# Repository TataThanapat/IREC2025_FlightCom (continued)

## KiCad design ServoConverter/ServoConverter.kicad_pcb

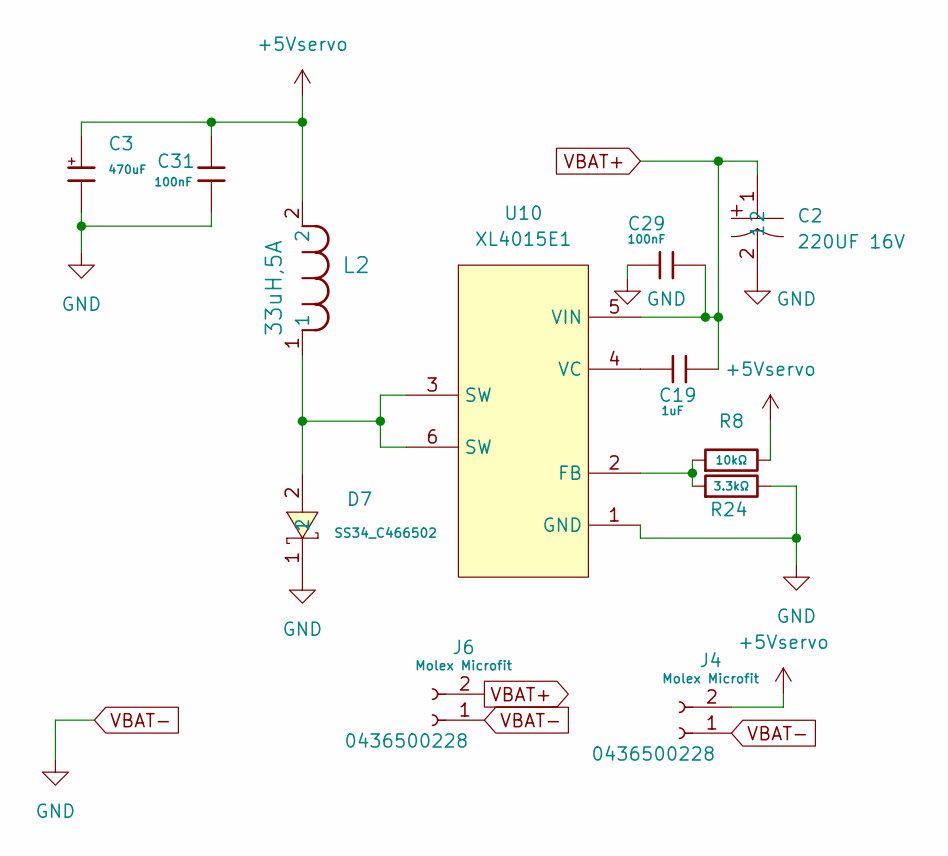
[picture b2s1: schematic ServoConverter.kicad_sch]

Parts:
C2: 220UF 16V; CAP-SMD_BD6.3-L6.6-W6.6-LS7.4-FD; LCSC Part C9900003178
C3: 470uF; CP_Elec_8x10; Voltage Rated 50V; Part EGT477M1HG16RRS0P; LCSC C3015599
C19: 1uF; C_0603; Voltage Rated 25V; Tolerance ±10%; Part CL05A105KA5NQNC; LCSC C52923
C29, C31: 100nF; C_0603; Voltage Rated 16V; Tolerance ±10%; Part CL05B104KO5NNNC; LCSC C1525
D7: SS34_C466502; DIOM7959X262N; LCSC Part C466502
J4, J6: Molex Microfit; Molex_Micro-Fit_3.0_43650-0215_1x02_P3.00mm_Vertical; Digikey Parts 0436500228
L2: 33uH,5A; L_Bourns_SRR1208_12.7x12.7mm; Digikey HCM1A1307V2-330-R
R8: 10kΩ; R_0603; Overload Voltage (Max) 75V; Tolerance ±1%; Part 0603WAF1002T5E; LCSC C25804
R24: 3.3kΩ; R_0603; Overload Voltage (Max) 75V; Tolerance ±1%; Part 0603WAF3301T5E; LCSC C22978
U10: XL4015E1; TO-263-5_L10.2-W8.9-P1.70-TL; LCSC Part C51661

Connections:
+5Vservo: C3.1, C31.2, J4.2, L2.2, R8.2
unnamed: D7.2, L2.1, U10.3 (SW), U10.6 (SW)
unnamed: R8.1, R24.1, U10.2 (FB)
unnamed: C19.1, U10.4 (VC)
VBAT+: C2.1, C19.2, C29.2, J6.2, U10.5 (VIN)
VBAT-: C2.2, C3.2, C29.1, C31.1, D7.1, J4.1, J6.1, R24.2, U10.1 (GND)

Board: 2 copper layers, 12 parts (0 on the bottom side), 6 nets, no tracks yet.

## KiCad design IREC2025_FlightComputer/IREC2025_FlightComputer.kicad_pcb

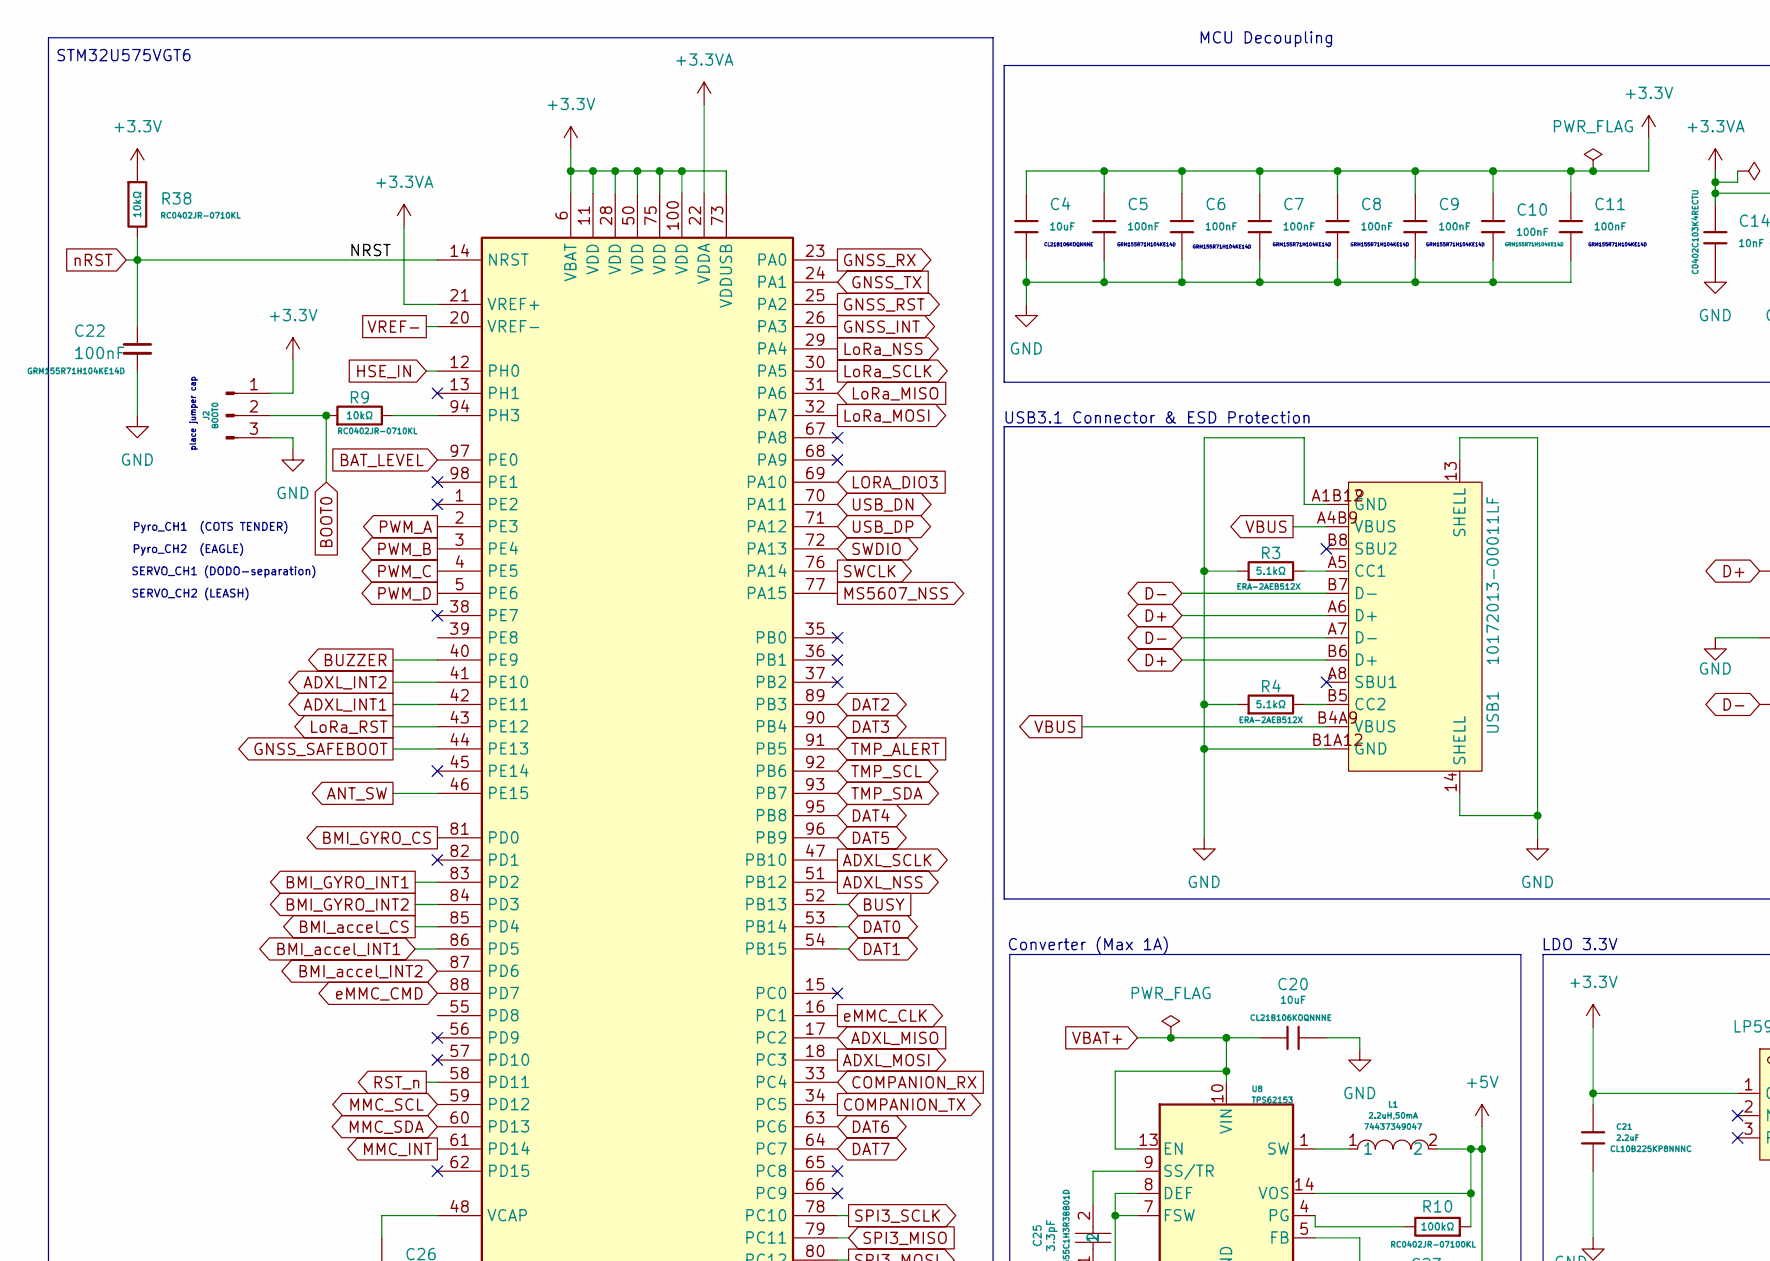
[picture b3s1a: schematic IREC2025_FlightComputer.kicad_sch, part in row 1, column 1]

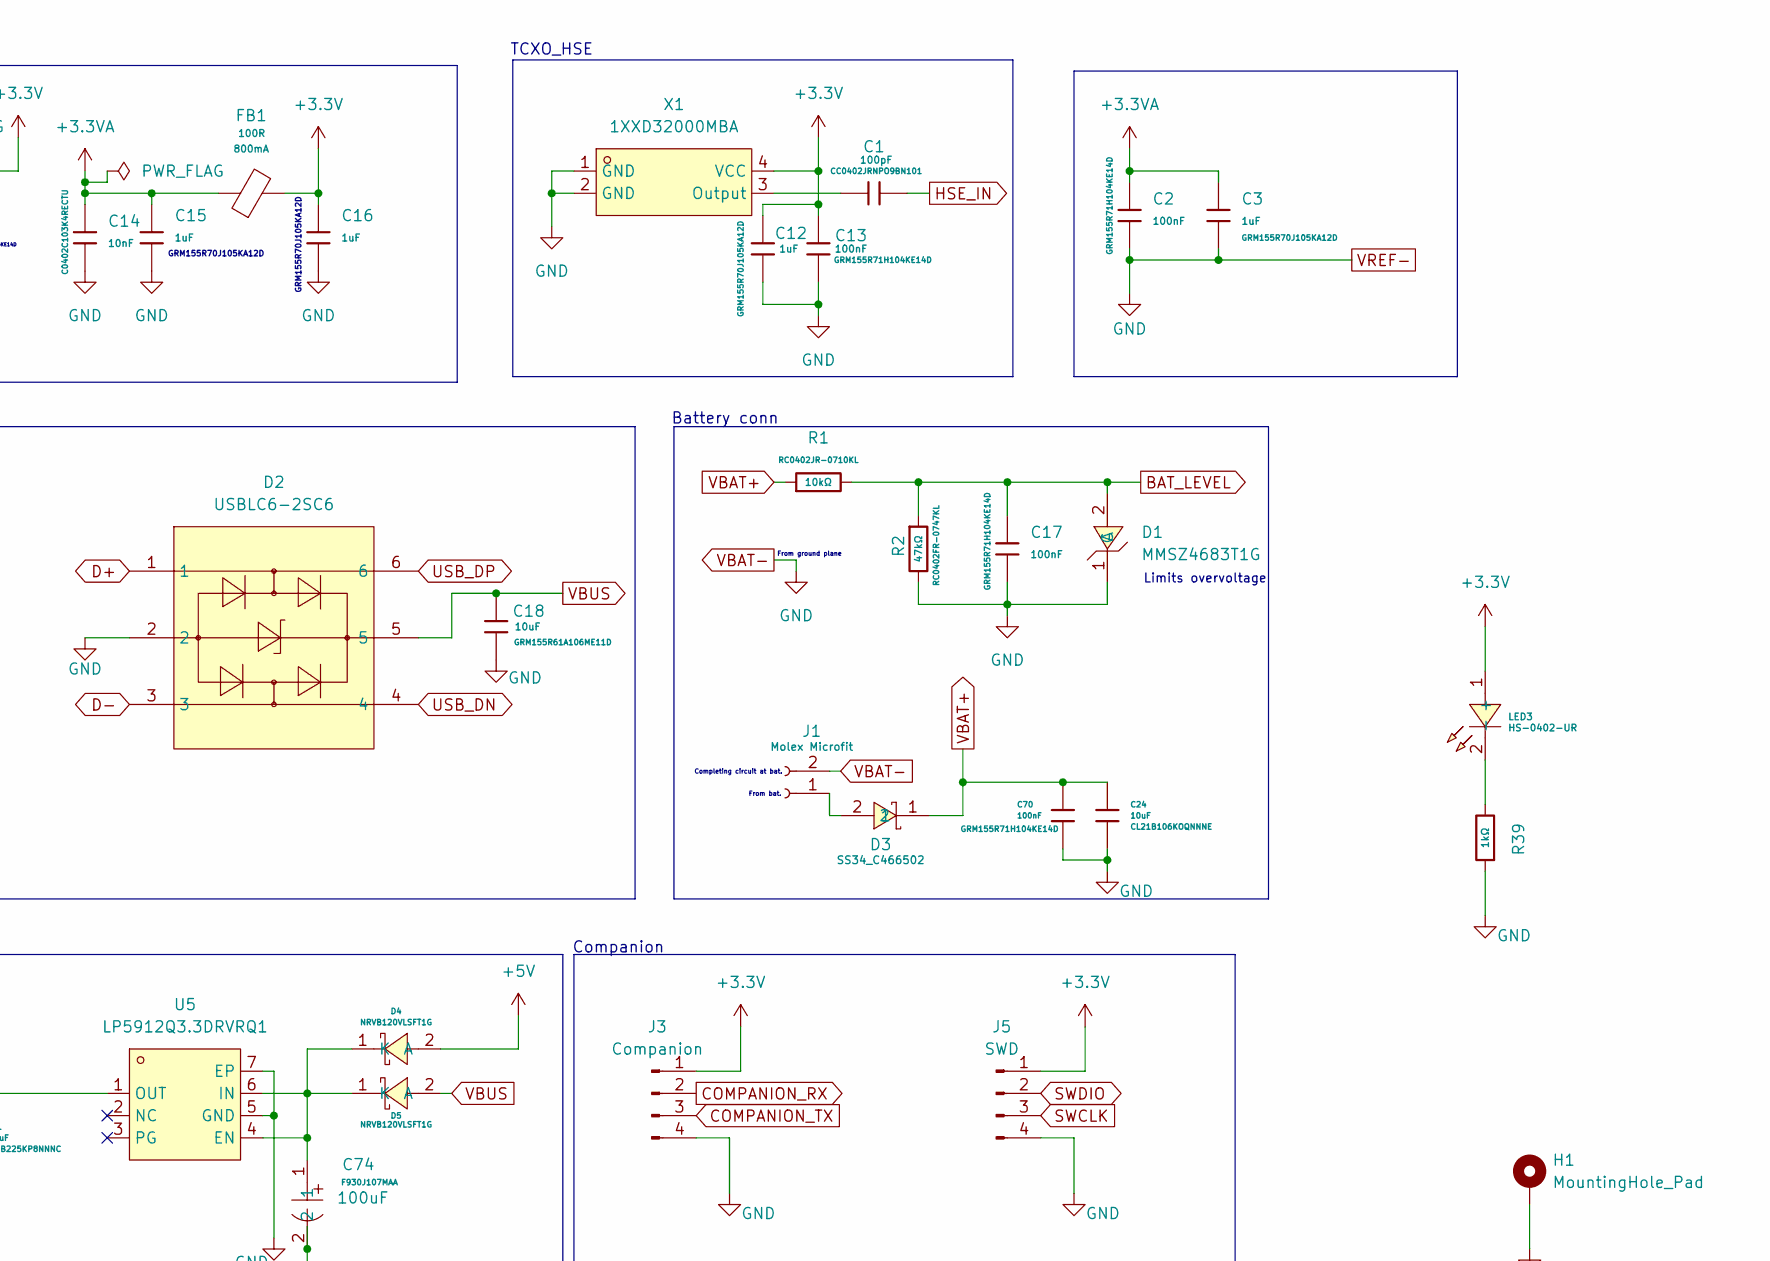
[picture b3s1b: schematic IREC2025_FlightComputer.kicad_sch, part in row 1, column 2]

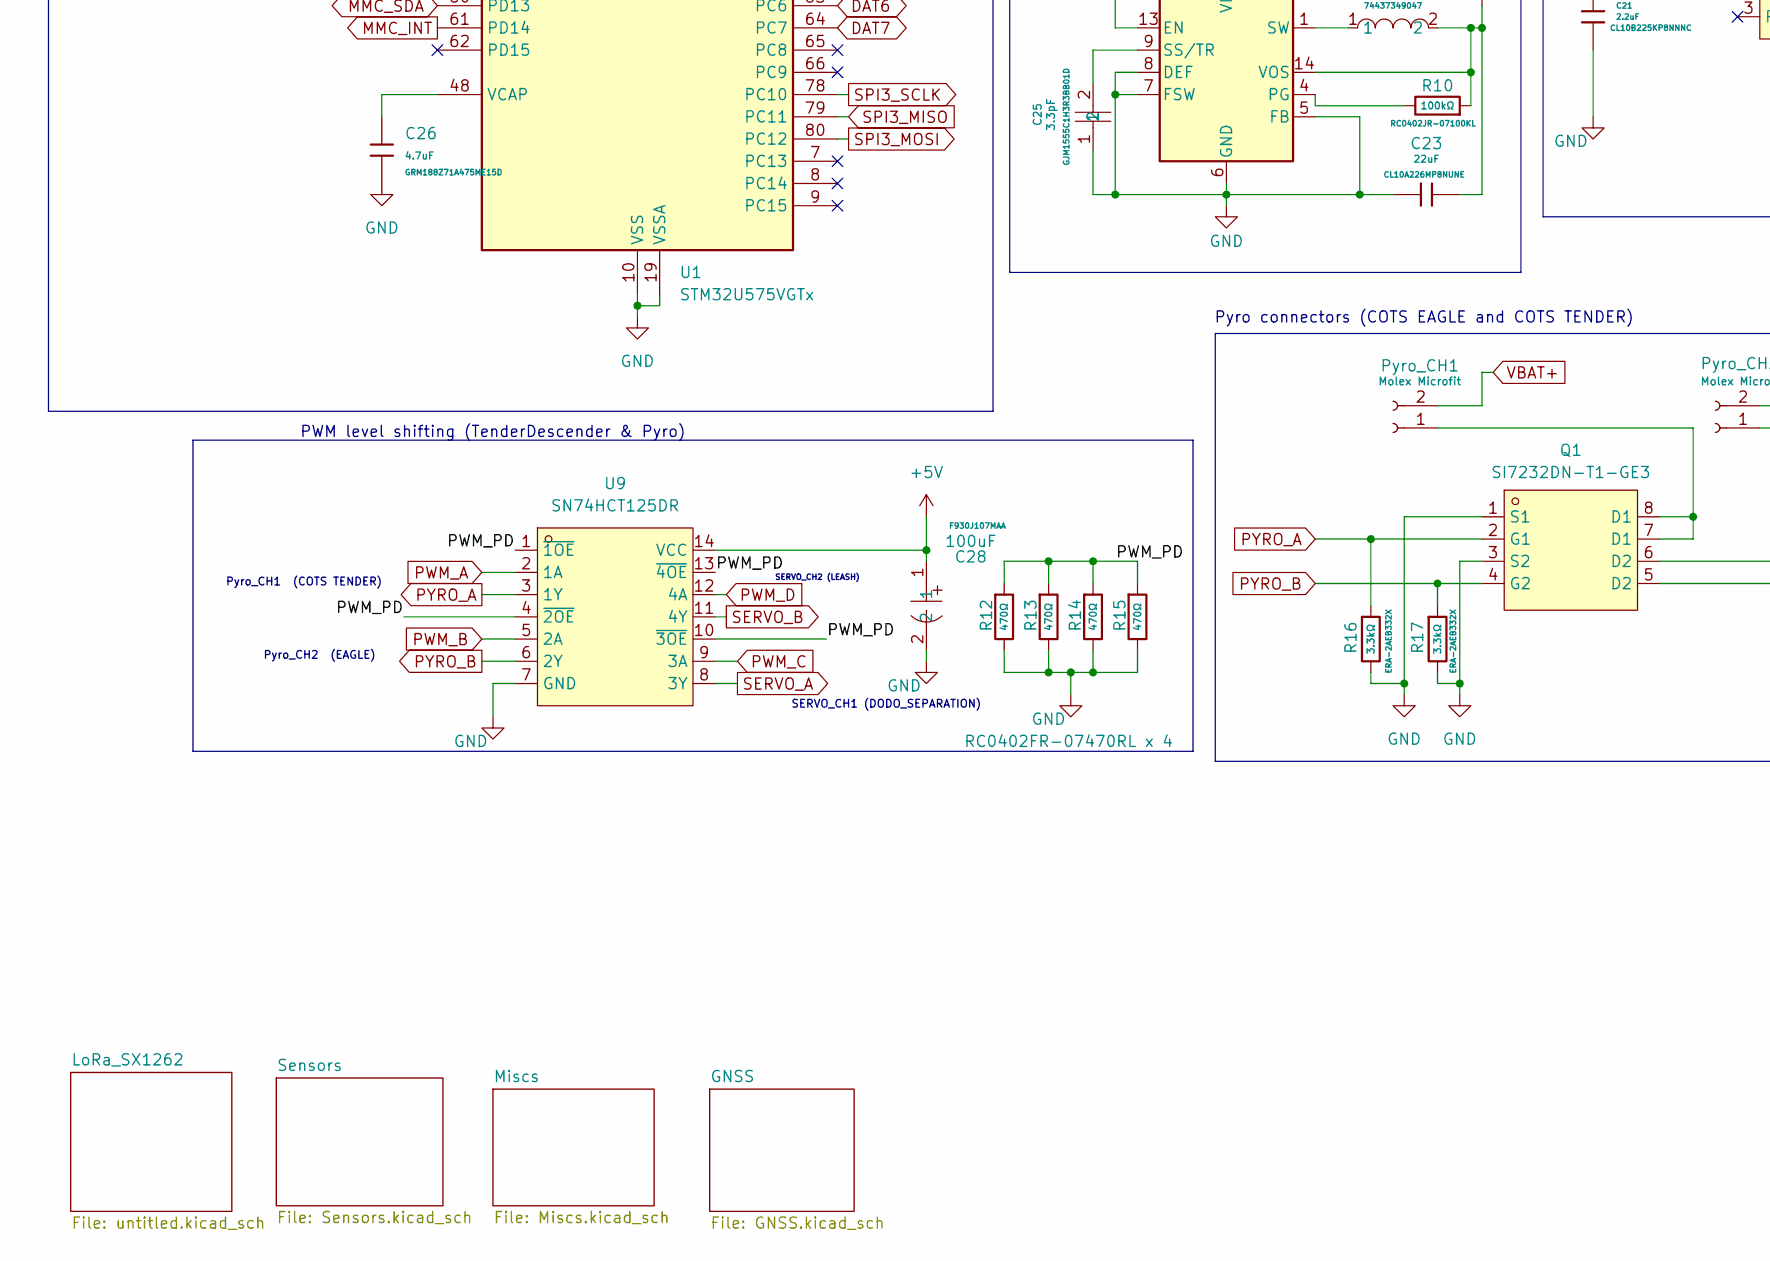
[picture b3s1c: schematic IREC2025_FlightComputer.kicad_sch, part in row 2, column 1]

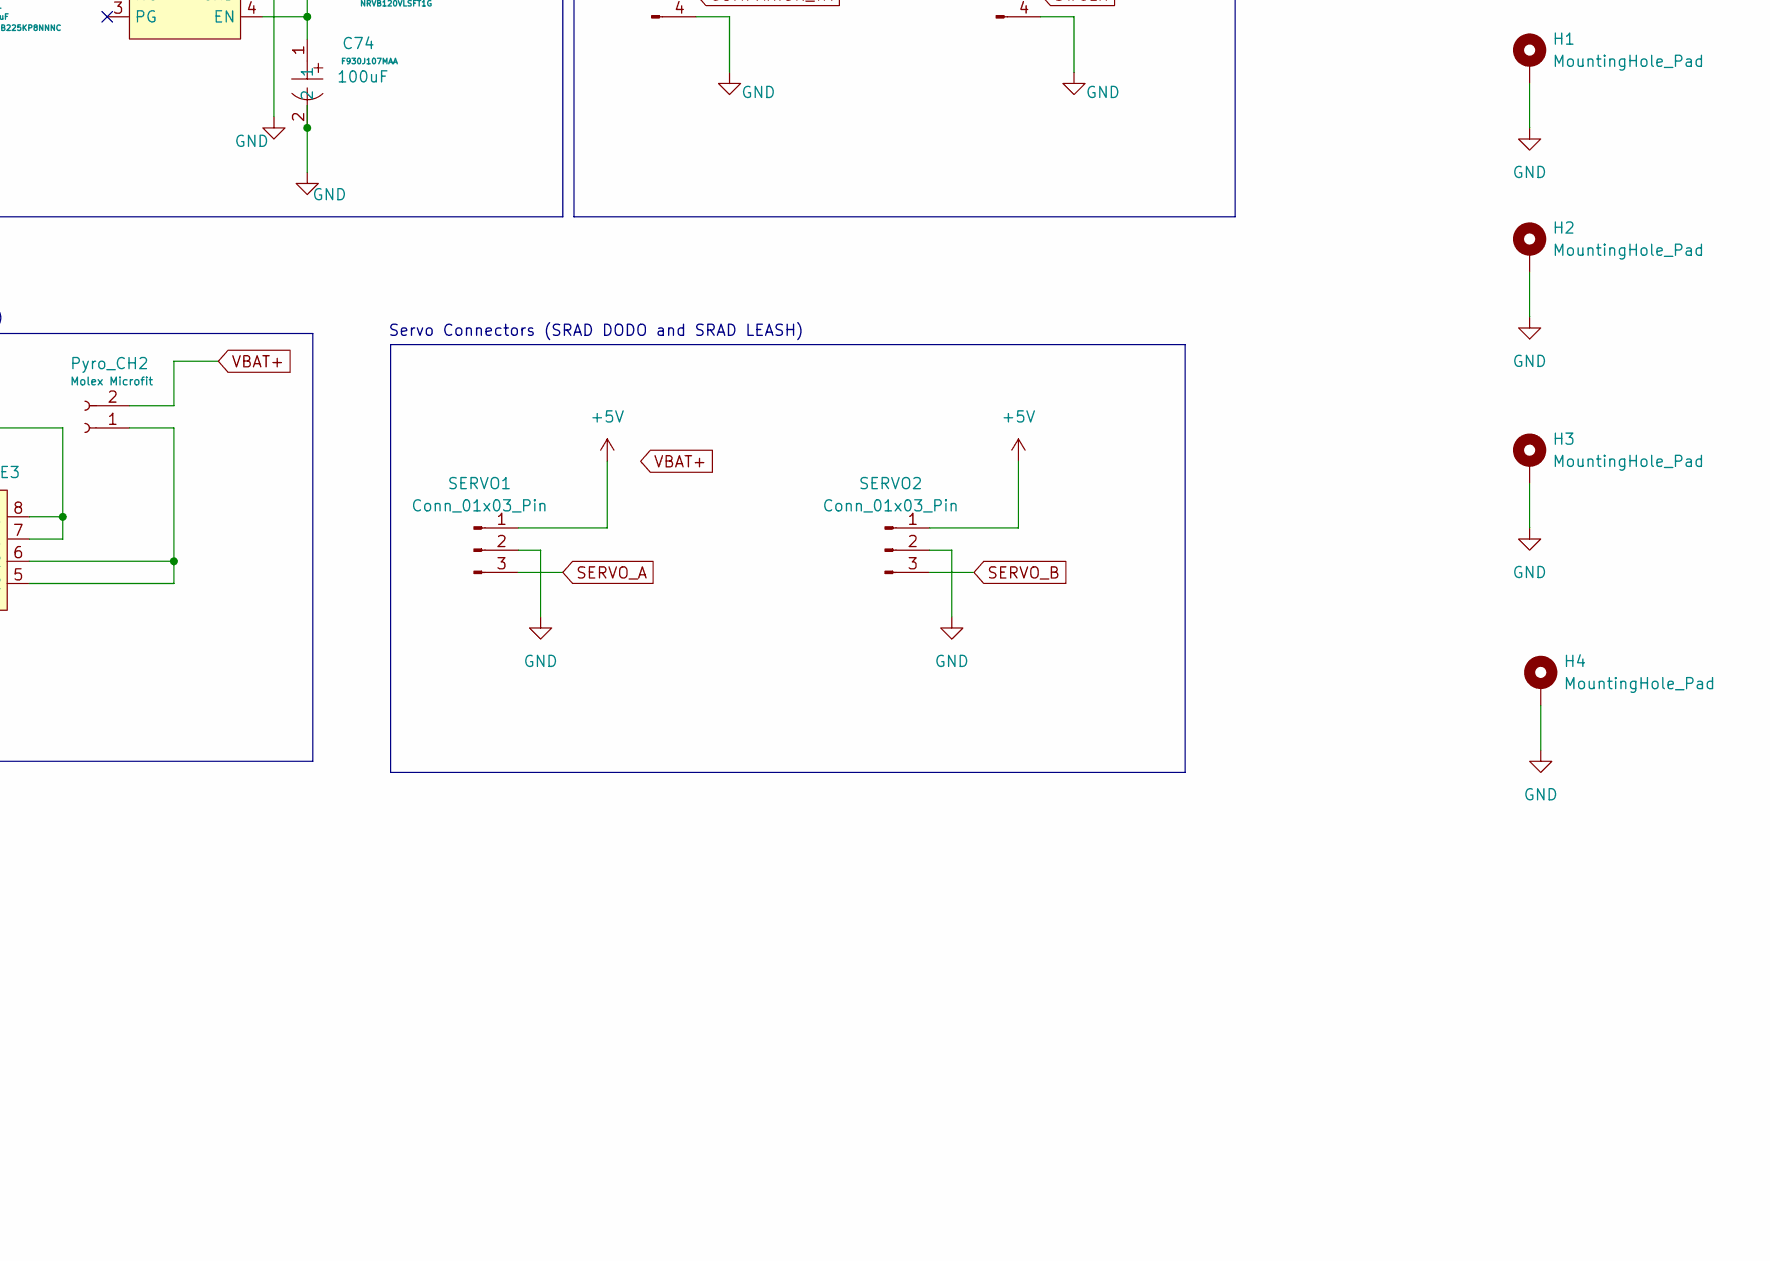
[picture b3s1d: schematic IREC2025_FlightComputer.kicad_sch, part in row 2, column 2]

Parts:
C1: 100pF; C_0402; Voltage Rated 50V; Tolerance ±5%; Part 0402CG101J500NT; LCSC C1546
C2, C5, C6, C7, C8, C9, C10, C11, C13, C17: 100nF; C_0402; Voltage Rated 16V; Tolerance ±10%; Part CL05B104KO5NNNC; LCSC C1525
C3, C12, C15, C16: 1uF; C_0402; Voltage Rated 25V; Tolerance ±10%; Part CL05A105KA5NQNC; LCSC C52923
C4: 10uF; C_0805; Voltage Rated 6.3V; Tolerance ±20%; Part CL05A106MQ5NUNC; LCSC C15525
C14: 10nF; C_0402; Voltage Rated 50V; Tolerance ±10%; Part CL05B103KB5NNNC; LCSC C15195
C18: 10uF; C_0402; Voltage Rated 6.3V; Tolerance ±20%; Part CL05A106MQ5NUNC; LCSC C15525
C20: 10uF; C_0805; Voltage Rated 25V; Tolerance ±20%; Part CL10A106MA8NRNC; LCSC C96446
C21: 2.2uF; C_0603; Voltage Rated 6.3V; Tolerance ±20%; Part CL05A225MQ5NSNC; LCSC C12530
C22: 100nF; C_0402
C23: 22uF; C_0603; Voltage Rated 6.3V; Tolerance ±20%; Part CL10A226MQ8NRNC; LCSC C59461
C24: 10uF; C_0805; Voltage Rated 50V; Tolerance ±10%; Part CL31A106KBHNNNE; LCSC C13585
C25: GJM1555C1H3R3BB01D; C0402; LCSC Part C76906
C26: 4.7uF; C_0603; Voltage Rated 10V; Tolerance ±20%; Part CL05A475MP5NRNC; LCSC C23733
C28, C74: 100uF; CAP-SMD_L3.2-W1.6; LCSC Part C561794
C70: 100nF; C_0402; Voltage Rated 50V; Tolerance ±10%; Part CL31B104KBCNNNC; LCSC C24497
D1: MMSZ4683T1G; SOD-123_L2.8-W1.8-LS3.7-RD; LCSC Part C235985
D2: USBLC6-2SC6; SOT-23-6_L2.9-W1.6-P0.95-LS2.8-BL; LCSC Part C7519
D3: SS34_C466502; DIOM7959X262N; LCSC Part C466502
D4, D5: NRVB120VLSFT1G; SOD-123_L2.7-W1.6-LS3.7-RD-1; LCSC Part C604264
FB1: 100R; FB_0805; Current Rating 800mA; Tolerance ±25%; Part GZ2012D101TF; LCSC C1015
H1, H2, H3, H4: MountingHole_Pad; MountingHole_3.2mm_M3_DIN965_Pad
J1: Molex Microfit; Molex_Micro-Fit_3.0_43650-0215_1x02_P3.00mm_Vertical
J2: BOOT0; PinHeader_1x03_P2.54mm_Vertical
J3: Companion; PinHeader_1x04_P2.54mm_Vertical
J5: SWD; PinHeader_1x04_P2.54mm_Vertical
L1: 2.2uH,50mA; IND-SMD_L4.0-W4.0_XFL4020-102MEB; LCSC Part C5156236
LED3: HS-0402-UR; LED0402-R-RD; LCSC Part C1322304
Pyro_CH1, Pyro_CH2: Molex Microfit; Molex_Micro-Fit_3.0_43650-0215_1x02_P3.00mm_Vertical
Q1: SI7232DN-T1-GE3; POWER-1212-8_L3.3-W3.3-P0.66-LS3.3-BL; LCSC Part C144854
R1, R9, R38: 10kΩ; R_0402; Overload Voltage (Max) 50V; Tolerance ±1%; Part 0402WGF1002TCE; LCSC C25744
R2: 47kΩ; R_0402; Overload Voltage (Max) 50V; Tolerance ±1%; Part 0402WGF4702TCE; LCSC C25792
R3, R4: 5.1kΩ; R_0402; Overload Voltage (Max) 50V; Tolerance ±1%; Part 0402WGF5101TCE; LCSC C25905
R10: 100kΩ; R_0402; Overload Voltage (Max) 50V; Tolerance ±1%; Part 0402WGF1003TCE; LCSC C25741
R12, R13, R14, R15: 470Ω; R_0402; Overload Voltage (Max) 50V; Tolerance ±1%; Part 0402WGF4700TCE; LCSC C25117
R16, R17: 3.3kΩ; R_0402; Overload Voltage (Max) 50V; Tolerance ±1%; Part 0402WGF3301TCE; LCSC C25890
R39: 1kΩ; R_0402; Overload Voltage (Max) 50V; Tolerance ±1%; Part 0402WGF1001TCE; LCSC C11702
SERVO1, SERVO2: Conn_01x03_Pin; Molex_Micro-Fit_3.0_43650-0315_1x03_P3.00mm_Vertical
U1: STM32U575VGTx; LQFP-100_14x14mm_P0.5mm
U5: LP5912Q3.3DRVRQ1; WSON-6_L2.0-W2.0-P0.65-TL-EP; LCSC Part C575581
U8: TPS62153; VQFN-16-1EP_3x3mm_P0.5mm_EP1.68x1.68mm_ThermalVias
U9: SN74HCT125DR; SOIC-14_L8.7-W3.9-P1.27-LS6.0-BL; LCSC Part C352957
USB1: 10172013-00011LF; USB-C-SMD_10174570-00A11LF; LCSC Part C22466647
X1: 1XXD32000MBA; OSC-SMD_4P-L2.0-W1.6-BL_1XXD; LCSC Part C253694

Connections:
+3.3V: C4.1, C5.1, C6.1, C7.1, C8.1, C9.1, C10.1, C11.1, C12.1, C13.1, C16.1, C21.1, FB1.2, J2.1, J3.1, J5.1, LED3.1 (+), R38.1, U1.6 (VBAT), U1.11 (VDD), U1.28 (VDD), U1.50 (VDD), U1.73 (VDDUSB), U1.75 (VDD), U1.100 (VDD), U5.1 (OUT), X1.4 (VCC); also elsewhere on the board
+3.3VA: C2.1, C3.1, C14.1, C15.1, FB1.1, U1.21 (VREF+), U1.22 (VDDA)
+5V: C23.2, C28.1, D4.2 (A), L1.2, R10.1, SERVO1.1, SERVO2.1, U8.14 (VOS), U9.14 (VCC)
/PWM_PD: R12.1, R13.1, R14.1, R15.1, U9.1 (~1OE), U9.4 (~2OE), U9.10 (~3OE), U9.13 (~4OE)
ADXL_INT1: U1.42 (PE11); also elsewhere on the board
ADXL_INT2: U1.41 (PE10); also elsewhere on the board
ADXL_MISO: U1.17 (PC2); also elsewhere on the board
ADXL_MOSI: U1.18 (PC3); also elsewhere on the board
ADXL_NSS: U1.51 (PB12); also elsewhere on the board
ADXL_SCLK: U1.47 (PB10); also elsewhere on the board
ANT_SW: U1.46 (PE15); also elsewhere on the board
BAT_LEVEL: C17.1, D1.2 (A), R1.2, R2.1, U1.97 (PE0)
BMI_GYRO_CS: U1.81 (PD0); also elsewhere on the board
BMI_GYRO_INT1: U1.83 (PD2); also elsewhere on the board
BMI_GYRO_INT2: U1.84 (PD3); also elsewhere on the board
BMI_accel_CS: U1.85 (PD4); also elsewhere on the board
BMI_accel_INT1: U1.86 (PD5); also elsewhere on the board
BMI_accel_INT2: U1.87 (PD6); also elsewhere on the board
BOOT0: J2.2, R9.1
BUSY: U1.52 (PB13); also elsewhere on the board
BUZZER: U1.40 (PE9); also elsewhere on the board
COMPANION_RX: J3.2, U1.33 (PC4)
COMPANION_TX: J3.3, U1.34 (PC5)
D+: D2.1, USB1.A6 (D+), USB1.B6 (D+)
D-: D2.3, USB1.A7 (D-), USB1.B7 (D-)
DAT0: U1.53 (PB14); also elsewhere on the board
DAT1: U1.54 (PB15); also elsewhere on the board
DAT2: U1.89 (PB3); also elsewhere on the board
DAT3: U1.90 (PB4); also elsewhere on the board
DAT4: U1.95 (PB8); also elsewhere on the board
DAT5: U1.96 (PB9); also elsewhere on the board
DAT6: U1.63 (PC6); also elsewhere on the board
DAT7: U1.64 (PC7); also elsewhere on the board
GNSS_INT: U1.26 (PA3); also elsewhere on the board
GNSS_RST: U1.25 (PA2); also elsewhere on the board
GNSS_RX: U1.23 (PA0); also elsewhere on the board
GNSS_SAFEBOOT: U1.44 (PE13); also elsewhere on the board
GNSS_TX: U1.24 (PA1); also elsewhere on the board
HSE_IN: C1.2, U1.12 (PH0)
LORA_DIO3: U1.69 (PA10); also elsewhere on the board
LoRa_MISO: U1.31 (PA6); also elsewhere on the board
LoRa_MOSI: U1.32 (PA7); also elsewhere on the board
LoRa_NSS: U1.29 (PA4); also elsewhere on the board
LoRa_RST: U1.43 (PE12); also elsewhere on the board
LoRa_SCLK: U1.30 (PA5); also elsewhere on the board
MMC_INT: U1.61 (PD14); also elsewhere on the board
MMC_SCL: U1.59 (PD12); also elsewhere on the board
MMC_SDA: U1.60 (PD13); also elsewhere on the board
MS5607_NSS: U1.77 (PA15); also elsewhere on the board
unnamed: C74.1, D4.1 (K), D5.1 (K), U5.4 (EN), U5.6 (IN)
unnamed: D3.2, J1.1
unnamed: L1.1, U8.1 (SW), U8.2 (SW), U8.3 (SW)
unnamed: LED3.2 (-), R39.2
unnamed: Pyro_CH1.1, Q1.7 (D1), Q1.8 (D1)
unnamed: Pyro_CH2.1, Q1.5 (D2), Q1.6 (D2)
unnamed: R9.2, U1.94 (PH3)
unnamed: C26.1, U1.48 (VCAP)
unnamed: R10.2, U8.4 (PG)
unnamed: C25.2, U8.9 (SS/TR)
unnamed: R3.2, USB1.A5 (CC1)
unnamed: R4.2, USB1.B5 (CC2)
unnamed: C1.1, X1.3 (Output)
PWM_A: U1.2 (PE3), U9.2 (1A)
PWM_B: U1.3 (PE4), U9.5 (2A)
PWM_C: U1.4 (PE5), U9.9 (3A)
PWM_D: U1.5 (PE6), U9.12 (4A)
PYRO_A: Q1.2 (G1), R16.1, U9.3 (1Y)
PYRO_B: Q1.4 (G2), R17.1, U9.6 (2Y)
RST_n: U1.58 (PD11); also elsewhere on the board
SERVO_A: SERVO1.3, U9.8 (3Y)
SERVO_B: SERVO2.3, U9.11 (4Y)
SWCLK: J5.3, U1.76 (PA14)
SWDIO: J5.2, U1.72 (PA13)
TMP_ALERT: U1.91 (PB5); also elsewhere on the board
TMP_SCL: U1.92 (PB6); also elsewhere on the board
TMP_SDA: U1.93 (PB7); also elsewhere on the board
USB_DN: D2.4, U1.70 (PA11)
USB_DP: D2.6, U1.71 (PA12)
VBAT+: C20.1, C24.1, C70.1, D3.1, Pyro_CH1.2, Pyro_CH2.2, R1.1, U8.10 (VIN), U8.11 (VIN), U8.12 (VIN), U8.13 (EN)
VBAT-: C2.2, C3.2, C4.2, C5.2, C6.2, C7.2, C8.2, C9.2, C10.2, C11.2, C12.2, C13.2, C14.2, C15.2, C16.2, C17.2, C18.2, C20.2, C21.2, C22.2, C23.1, C24.2, C25.1, C26.2, C28.2, C70.2, C74.2, D1.1 (C), D2.2, H1.1, H2.1, H3.1, H4.1, J1.2, J2.3, J3.4, J5.4, Q1.1 (S1), Q1.3 (S2), R2.2, R3.1, R4.1, R12.2, R13.2, R14.2, R15.2, R16.2, R17.2, R39.1, SERVO1.2, SERVO2.2, U1.10 (VSS), U1.19 (VSSA), U1.20 (VREF-), U1.27 (VSS), U1.49 (VSS), U1.74 (VSS), U1.99 (VSS), U5.5 (GND), U5.7 (EP), U8.5 (FB), U8.6 (GND), U8.7 (FSW), U8.8 (DEF), U8.15 (GND), U8.16 (GND), U8.17 (GND), U9.7 (GND), USB1.13 (SHELL), USB1.14 (SHELL), USB1.A1B12 (GND), USB1.B1A12 (GND), X1.1 (GND), X1.2 (GND); also elsewhere on the board
VBUS: C18.1, D2.5, D5.2 (A), USB1.A4B9 (VBUS), USB1.B4A9 (VBUS)
eMMC_CLK: U1.16 (PC1); also elsewhere on the board
eMMC_CMD: U1.88 (PD7); also elsewhere on the board
nRST: C22.1, R38.2, U1.14 (NRST)

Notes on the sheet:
Pyro connectors (COTS EAGLE and COTS TENDER)
PWM level shifting (TenderDescender & Pyro)
LDO 3.3V
SERVO_CH2 (LEASH)
Pyro_CH2 (EAGLE)
STM32U575VGT6
GRM155R71H104KE14D
Battery conn
Completing circuit at bat.
Pyro_CH1 (COTS TENDER)
CL21B106KOQNNNE
Limits overvoltage
SERVO_CH1 (DODO_SEPARATION)
Converter (Max 1A)
GRM155R70J105KA12D
Servo Connectors (SRAD DODO and SRAD LEASH)
From ground plane
place jumper cap
MCU Decoupling
SERVO_CH1 (DODO-separation)
From bat.
TCXO_HSE
USB3.1 Connector & ESD Protection
Companion

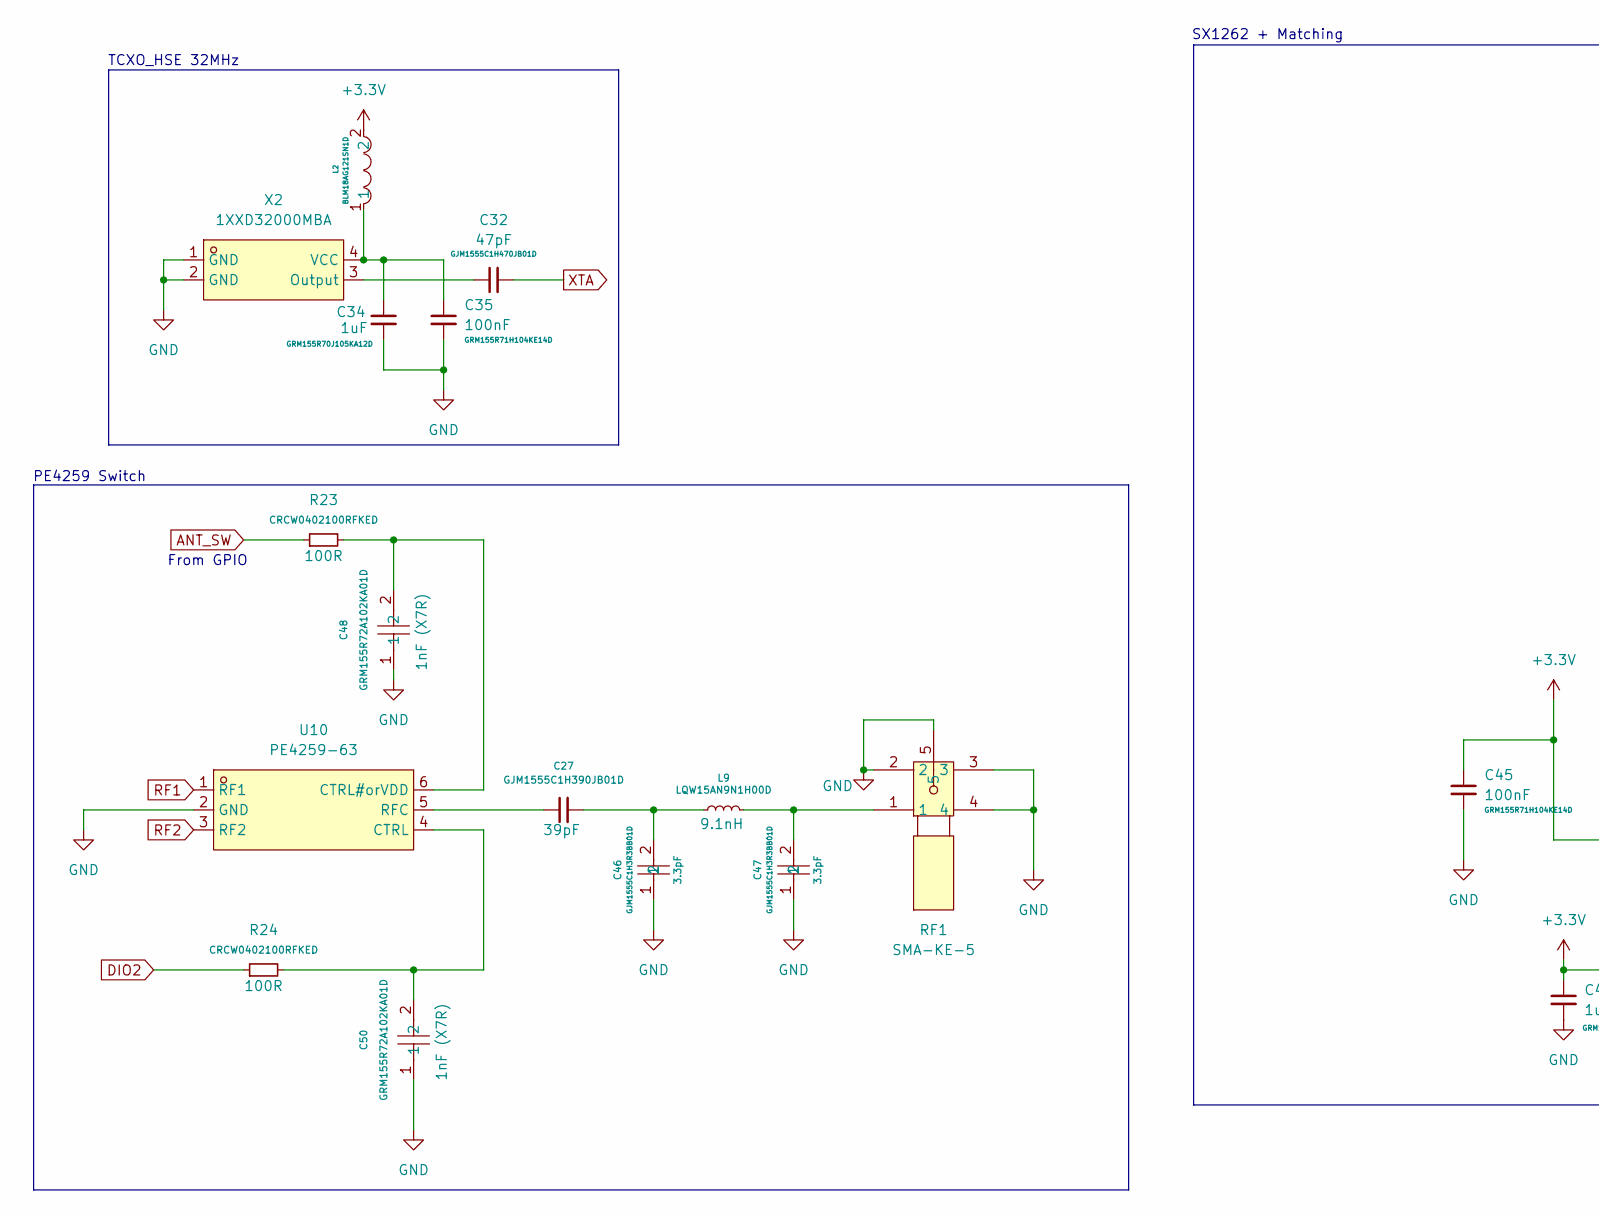
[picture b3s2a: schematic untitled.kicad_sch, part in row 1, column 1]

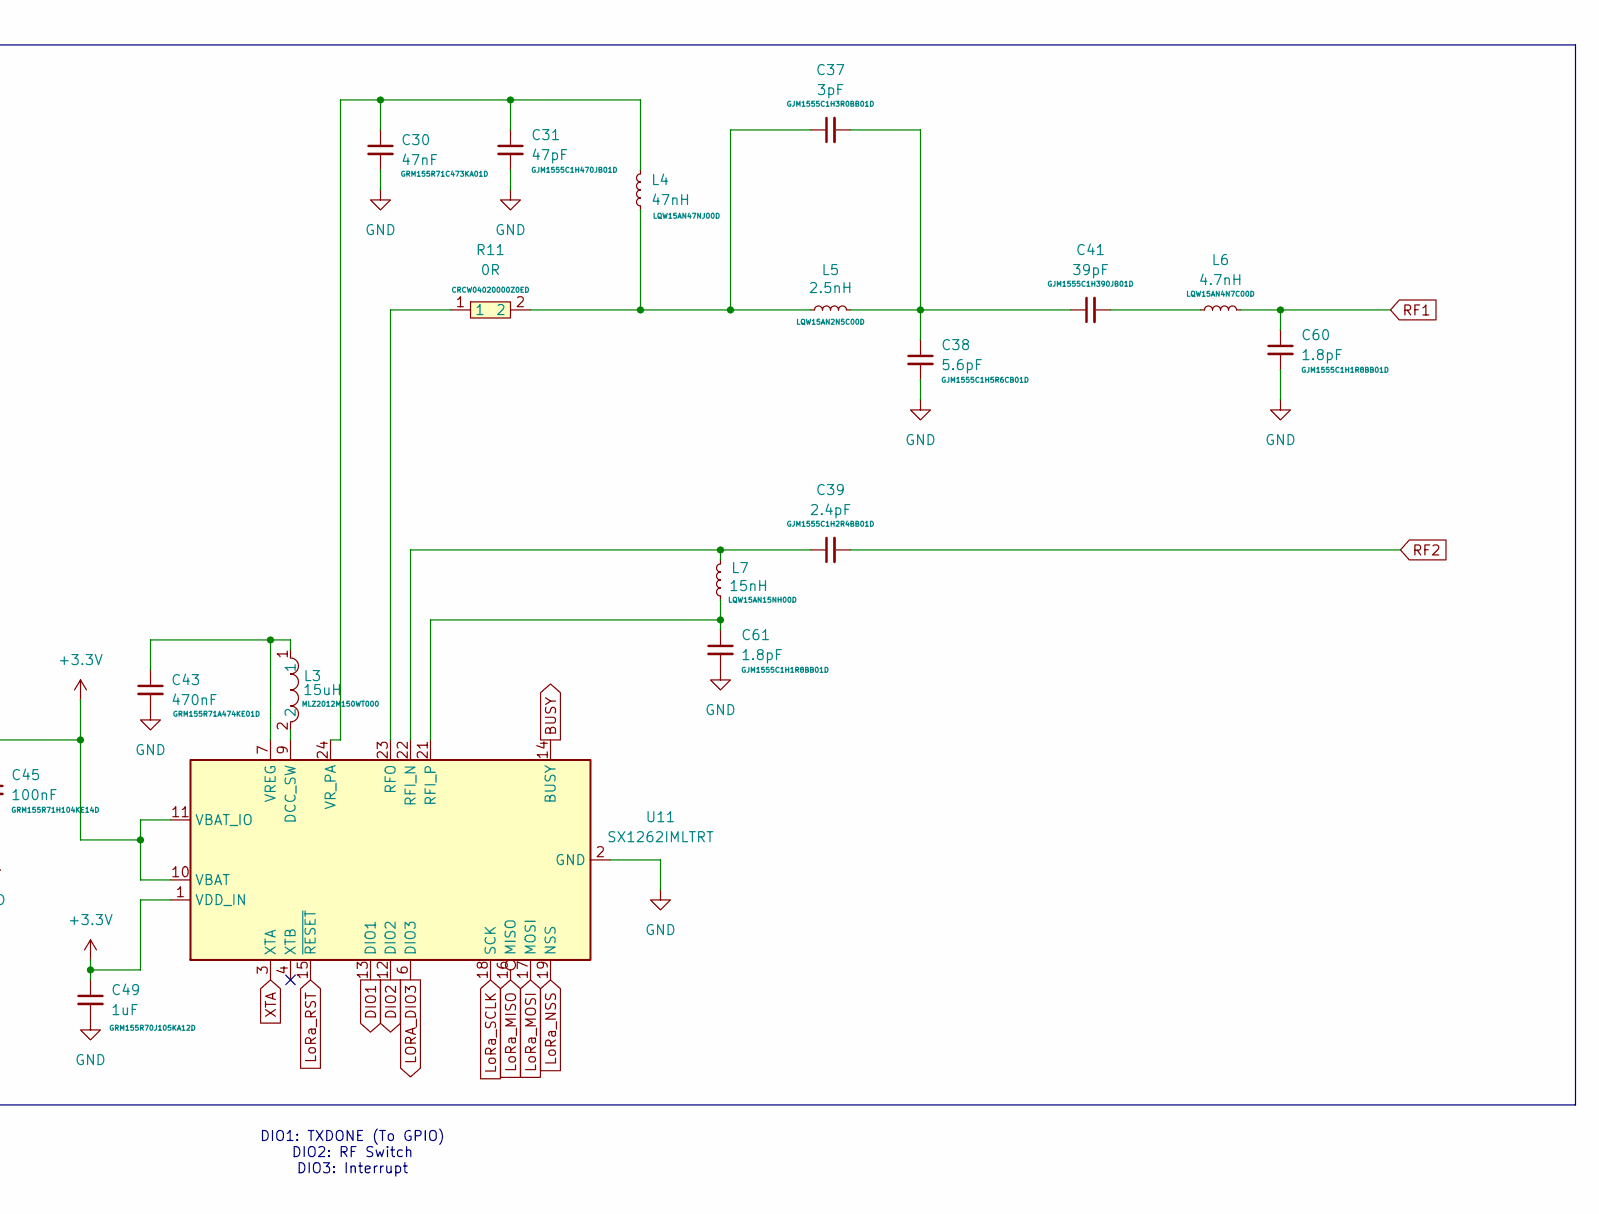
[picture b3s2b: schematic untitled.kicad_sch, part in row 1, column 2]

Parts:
C27: GJM1555C1H390JB01D; C_0402
C30: 47nF; C_0402
C31, C32: 47pF; C_0402
C34, C49: 1uF; C_0402
C35, C45: 100nF; C_0402
C37: 3pF; C_0402
C38: 5.6pF; C_0402
C39: 2.4pF; C_0402
C41: 39pF; C_0402
C43: 470nF; C_0402
C46, C47: GJM1555C1H3R3BB01D; C0402; LCSC Part C76906
C48, C50: GRM155R72A102KA01D; C0402; LCSC Part C162197
C60, C61: 1.8pF; C_0402
L2: BLM18AG121SN1D; L0603; LCSC Part C76892
L3: 15uH; L0805; LCSC Part C383402
L4: 47nH; L_0402
L5: 2.5nH; C_0402; Part LQW15AN2N5C00D
L6: 4.7nH; L_0402_1005Metric
L7: 15nH; L_0402_1005Metric
L9: LQW15AN9N1H00D; L_0402_1005Metric
R11: 0R; R_0402; LCSC Part C190119
R23, R24: CRCW0402100RFKED; R_0402
RF1: SMA-KE-5; SMA-TH_SMA-KHDB_C9900020423; LCSC Part C20415804
U10: PE4259-63; SC-70-6_L2.2-W1.3-P0.65-LS2.1-BL; LCSC Part C470892
U11: SX1262IMLTRT; QFN-24-1EP_4x4mm_P0.5mm_EP2.6x2.6mm
X2: 1XXD32000MBA; OSC-SMD_4P-L2.0-W1.6-BL_1XXD; LCSC Part C253694

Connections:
+3.3V: C45.1, C49.1, L2.2, U11.1 (VDD_IN), U11.10 (VBAT), U11.11 (VBAT_IO); also elsewhere on the board
ANT_SW: R23.1; also elsewhere on the board
BUSY: U11.14 (BUSY); also elsewhere on the board
DIO1: U11.13 (DIO1)
DIO2: R24.1, U11.12 (DIO2)
LORA_DIO3: U11.6 (DIO3); also elsewhere on the board
LoRa_MISO: U11.16 (MISO); also elsewhere on the board
LoRa_MOSI: U11.17 (MOSI); also elsewhere on the board
LoRa_NSS: U11.19 (NSS); also elsewhere on the board
LoRa_RST: U11.15 (~RESET); also elsewhere on the board
LoRa_SCLK: U11.18 (SCK); also elsewhere on the board
unnamed: C27.2, C46.2, L9.1
unnamed: C37.1, L4.1, L5.1, R11.2
unnamed: C37.2, C38.1, C41.1, L5.2
unnamed: C41.2, L6.1
unnamed: C47.2, L9.2, RF1.1
unnamed: C48.2, R23.2, U10.6 (CTRL#orVDD)
unnamed: C50.2, R24.2, U10.4 (CTRL)
unnamed: C27.1, U10.5 (RFC)
unnamed: L3.2, U11.9 (DCC_SW)
unnamed: C39.1, L7.2, U11.22 (RFI_N)
unnamed: C61.1, L7.1, U11.21 (RFI_P)
unnamed: R11.1, U11.23 (RFO)
unnamed: C43.1, L3.1, U11.7 (VREG)
unnamed: C30.1, C31.1, L4.2, U11.24 (VR_PA)
unnamed: C32.1, X2.3 (Output)
unnamed: C34.1, C35.1, L2.1, X2.4 (VCC)
RF1: C60.1, L6.2, U10.1 (RF1)
RF2: C39.2, U10.3 (RF2)
VBAT-: C30.2, C31.2, C34.2, C35.2, C38.2, C43.2, C45.2, C46.1, C47.1, C48.1, C49.2, C50.1, C60.2, C61.2, RF1.2, RF1.3, RF1.4, RF1.5, U10.2 (GND), U11.2 (GND), U11.5 (GND), U11.8 (GND), U11.20 (GND), U11.25 (GND), X2.1 (GND), X2.2 (GND); also elsewhere on the board
XTA: C32.2, U11.3 (XTA)

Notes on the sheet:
SX1262 + Matching
PE4259 Switch
DIO1: TXDONE (To GPIO) DIO2: RF Switch DIO3: Interrupt
From GPIO
TCXO_HSE 32MHz
